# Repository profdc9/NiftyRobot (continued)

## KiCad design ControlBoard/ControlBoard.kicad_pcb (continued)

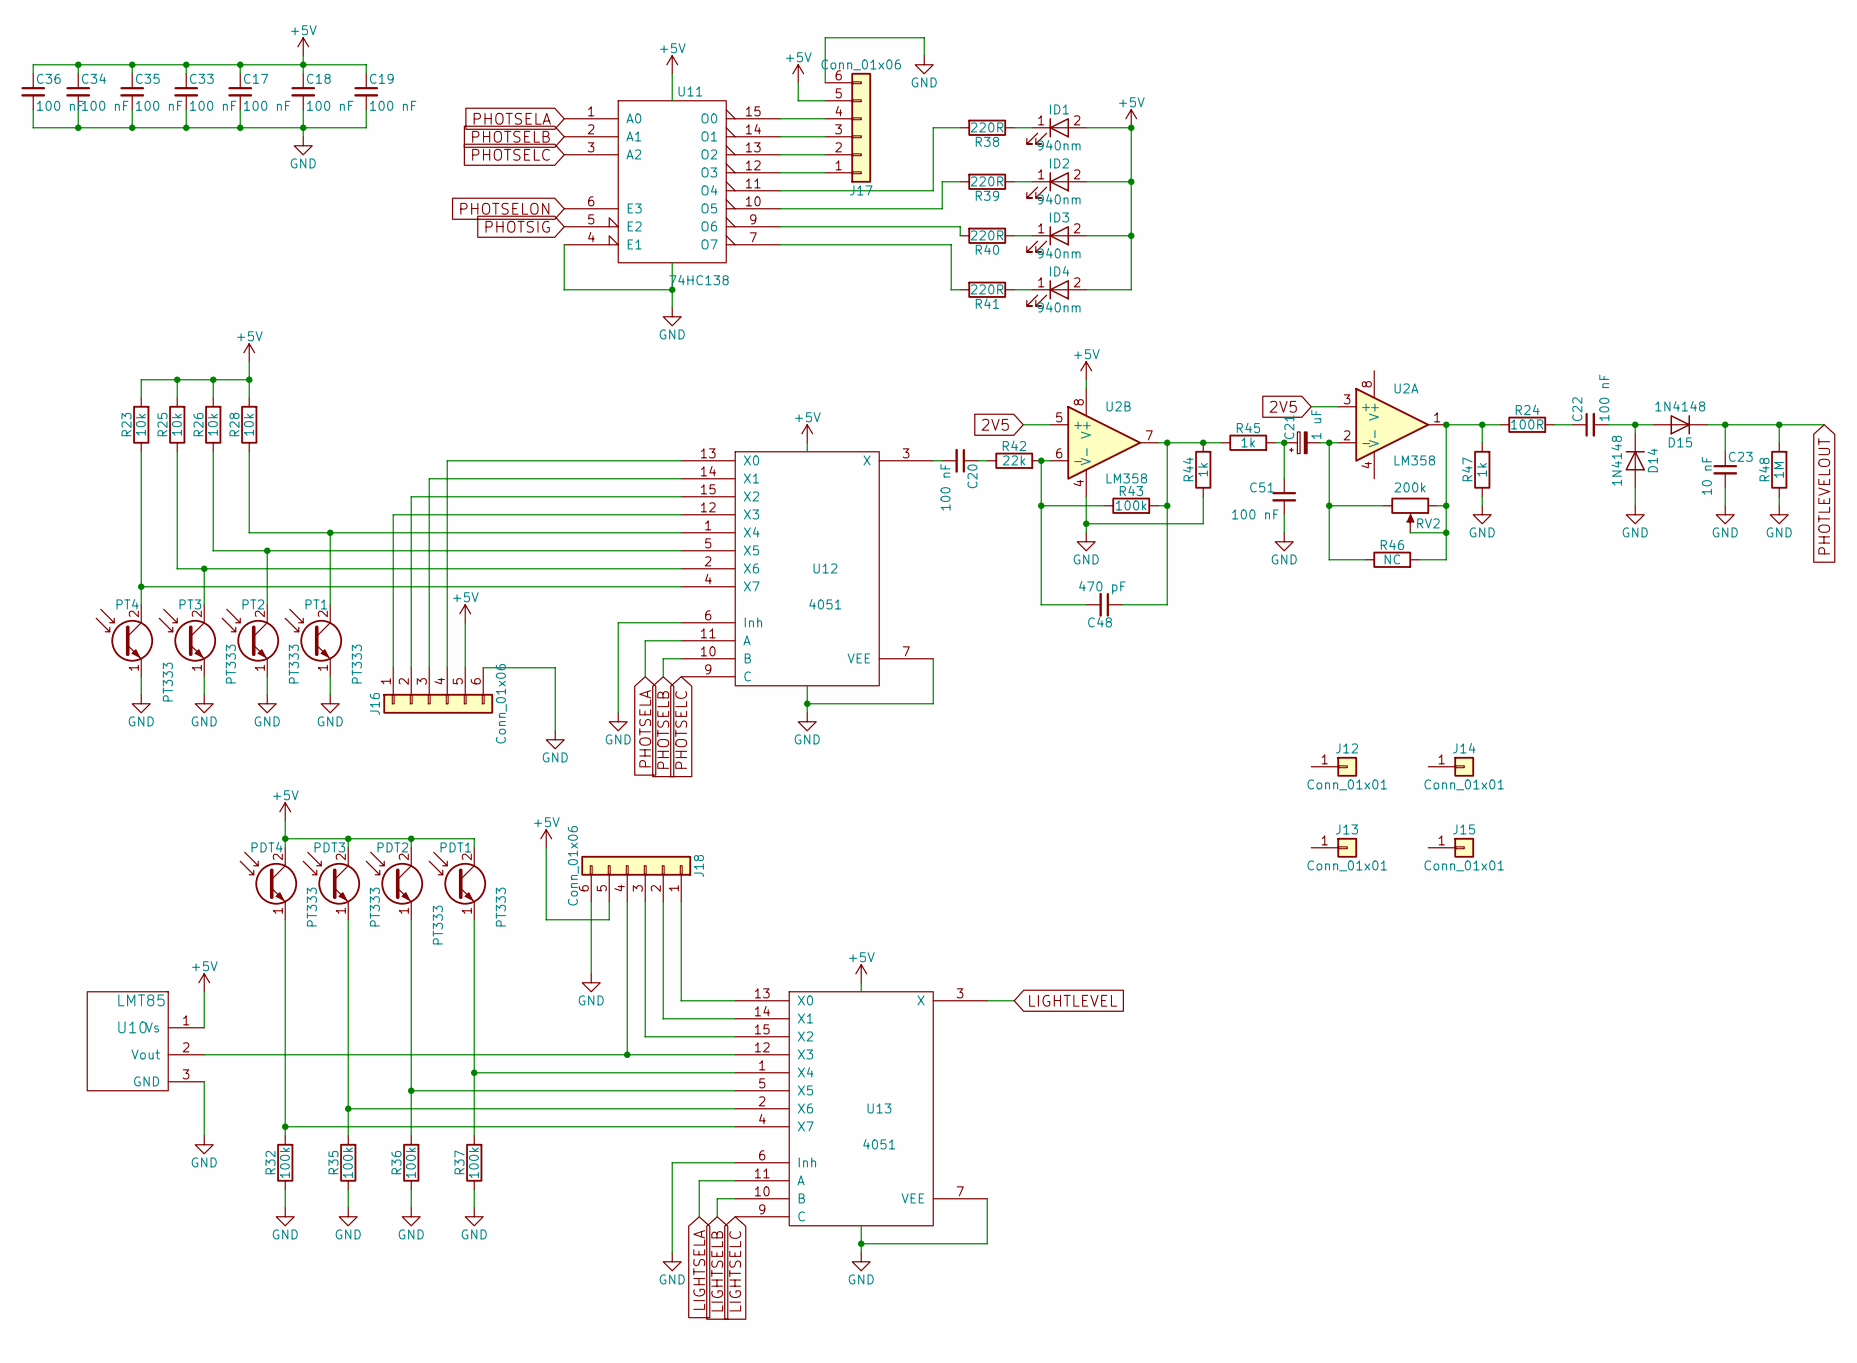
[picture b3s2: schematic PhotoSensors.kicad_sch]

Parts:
C17, C18, C19, C33, C34, C35, C36: 100 nF; C_Disc_D5.0mm_W2.5mm_P2.50mm
C20, C22, C51: 100 nF; C_Disc_D5.0mm_W2.5mm_P5.00mm
C21: 1 uF; CP_Radial_D5.0mm_P2.50mm
C23: 10 nF; C_Disc_D5.0mm_W2.5mm_P5.00mm
C48: 470 pF; C_Disc_D5.0mm_W2.5mm_P5.00mm
D14, D15: 1N4148; D_DO-41_SOD81_P7.62mm_Horizontal
ID1, ID2, ID3, ID4: 940nm; LED_D5.0mm
J12, J13, J14, J15: Conn_01x01; IRPair
J16, J17, J18: Conn_01x06; Pin_Header_Straight_1x06_Pitch2.54mm
PDT1, PDT2, PDT3, PDT4: PT333; LED_D5.0mm
PT1, PT2, PT3, PT4: PT333; LED_D5.0mm
R23, R25, R26, R28: 10k; R_Axial_DIN0207_L6.3mm_D2.5mm_P7.62mm_Horizontal
R24: 100R; R_Axial_DIN0207_L6.3mm_D2.5mm_P7.62mm_Horizontal
R32, R35, R36, R37, R43: 100k; R_Axial_DIN0207_L6.3mm_D2.5mm_P7.62mm_Horizontal
R38, R39, R40, R41: 220R; R_Axial_DIN0207_L6.3mm_D2.5mm_P7.62mm_Horizontal
R42: 22k; R_Axial_DIN0207_L6.3mm_D2.5mm_P7.62mm_Horizontal
R44, R45, R47: 1k; R_Axial_DIN0207_L6.3mm_D2.5mm_P7.62mm_Horizontal
R46: NC; R_Axial_DIN0207_L6.3mm_D2.5mm_P7.62mm_Horizontal
R48: 1M; R_Axial_DIN0207_L6.3mm_D2.5mm_P7.62mm_Horizontal
RV2: 200k; Potentiometer_Trimmer_Bourns_3296W
U2: LM358; DIP-8_W7.62mm_Socket
U10: LMT85; TO-92_Inline_Wide
U11: 74HC138; DIP-16_W7.62mm_Socket
U12, U13: 4051; DIP-16_W7.62mm_Socket

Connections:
2V5: U2.3 (+), U2.5 (+); also elsewhere on the board
+5V: C17.1, C18.1, C19.1, C33.1, C34.1, C35.1, C36.1, ID1.2 (A), ID2.2 (A), ID3.2 (A), ID4.2 (A), J16.5, J17.5, J18.5, PDT1.2 (C), PDT2.2 (C), PDT3.2 (C), PDT4.2 (C), R23.2, R25.2, R26.2, R28.2, U2.8 (V+), U10.1 (Vs), U11.16 (VCC), U12.16 (VDD), U13.16 (VDD); also elsewhere on the board
GND: C17.2, C18.2, C19.2, C23.2, C33.2, C34.2, C35.2, C36.2, C51.2, D14.2 (A), J16.6, J17.6, J18.6, PT1.1 (E), PT2.1 (E), PT3.1 (E), PT4.1 (E), R32.1, R35.1, R36.1, R37.1, R44.1, R47.1, R48.1, U2.4 (V-), U10.3 (GND), U11.4 (E1), U11.8 (GND), U12.6 (Inh), U12.7 (VEE), U12.8 (VSS), U13.6 (Inh), U13.7 (VEE), U13.8 (VSS); also elsewhere on the board
LIGHTLEVEL: U13.3 (X); also elsewhere on the board
LIGHTSELA: U13.11 (A); also elsewhere on the board
LIGHTSELB: U13.10 (B); also elsewhere on the board
LIGHTSELC: U13.9 (C); also elsewhere on the board
unnamed: C20.1, R42.1
unnamed: C21.1, C51.1, R45.2
unnamed: C22.1, R24.2
unnamed: C48.1, R43.2, R44.2, R45.1, U2.7
unnamed: C22.2, D14.1 (K), D15.2 (A)
unnamed: ID1.1 (K), R38.1
unnamed: ID2.1 (K), R39.1
unnamed: ID3.1 (K), R40.1
unnamed: ID4.1 (K), R41.1
unnamed: J16.1, U12.12 (X3)
unnamed: J16.2, U12.15 (X2)
unnamed: J16.3, U12.14 (X1)
unnamed: J16.4, U12.13 (X0)
unnamed: J17.1, U11.12 (O3)
unnamed: J17.2, U11.13 (O2)
unnamed: J17.3, U11.14 (O1)
unnamed: J17.4, U11.15 (O0)
unnamed: J18.1, U13.13 (X0)
unnamed: J18.2, U13.14 (X1)
unnamed: J18.3, U13.15 (X2)
unnamed: J18.4, U10.2 (Vout), U13.12 (X3)
unnamed: PDT1.1 (E), R37.2, U13.1 (X4)
unnamed: PDT2.1 (E), R36.2, U13.5 (X5)
unnamed: PDT3.1 (E), R35.2, U13.2 (X6)
unnamed: PDT4.1 (E), R32.2, U13.4 (X7)
unnamed: PT1.2 (C), R28.1, U12.1 (X4)
unnamed: PT2.2 (C), R26.1, U12.5 (X5)
unnamed: PT3.2 (C), R25.1, U12.2 (X6)
unnamed: PT4.2 (C), R23.1, U12.4 (X7)
unnamed: R24.1, R46.2, R47.2, RV2.1, RV2.2, U2.1
unnamed: C21.2, R46.1, RV2.3, U2.2 (-)
unnamed: C48.2, R42.2, R43.1, U2.6 (-)
unnamed: R38.2, U11.11 (O4)
unnamed: R39.2, U11.10 (O5)
unnamed: R40.2, U11.9 (O6)
unnamed: R41.2, U11.7 (O7)
unnamed: C20.2, U12.3 (X)
PHOTLEVELOUT: C23.1, D15.1 (K), R48.2; also elsewhere on the board
PHOTSELA: U11.1 (A0), U12.11 (A); also elsewhere on the board
PHOTSELB: U11.2 (A1), U12.10 (B); also elsewhere on the board
PHOTSELC: U11.3 (A2), U12.9 (C); also elsewhere on the board
PHOTSELON: U11.6 (E3); also elsewhere on the board
PHOTSIG: U11.5 (E2); also elsewhere on the board

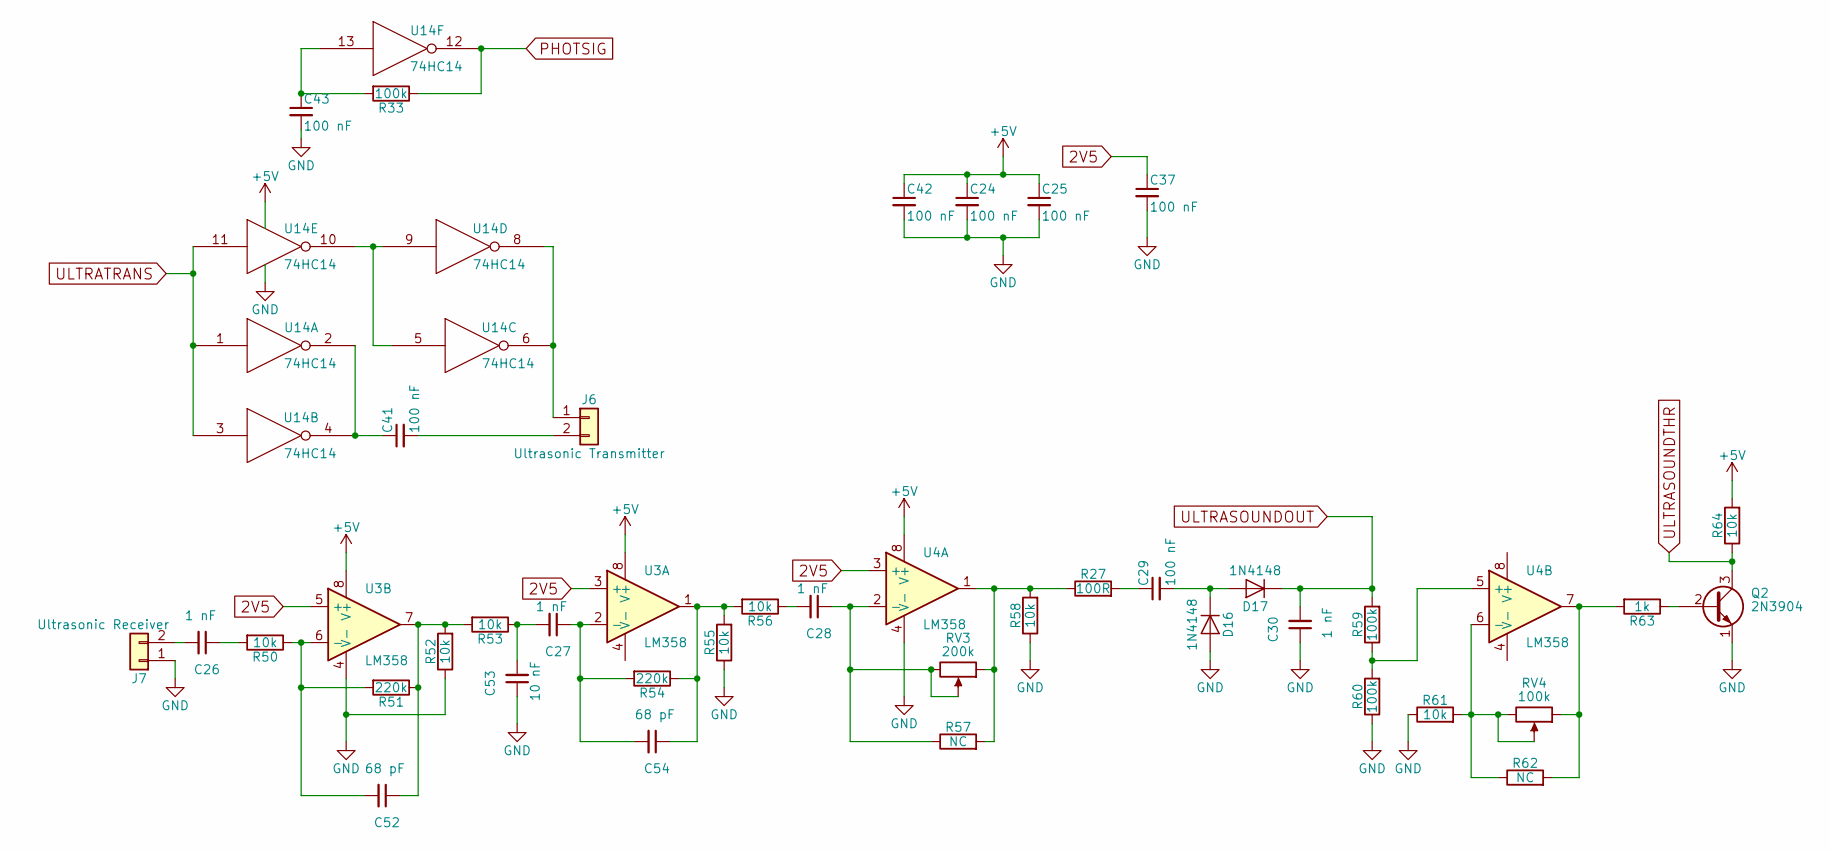
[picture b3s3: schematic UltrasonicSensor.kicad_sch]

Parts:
C24, C25, C29, C37, C41, C42, C43: 100 nF; C_Disc_D5.0mm_W2.5mm_P2.50mm
C26, C27, C28, C30: 1 nF; C_Disc_D5.0mm_W2.5mm_P5.00mm
C52, C54: 68 pF; C_Disc_D5.0mm_W2.5mm_P5.00mm
C53: 10 nF; C_Disc_D5.0mm_W2.5mm_P5.00mm
D16, D17: 1N4148; D_DO-41_SOD81_P7.62mm_Horizontal
J6: Ultrasonic Transmitter; TerminalBlock_bornier-2_P5.08mm
J7: Ultrasonic Receiver; TerminalBlock_bornier-2_P5.08mm
Q2: 2N3904; TO-92_Inline_Wide
R27: 100R; R_Axial_DIN0207_L6.3mm_D2.5mm_P7.62mm_Horizontal
R33, R59, R60: 100k; R_Axial_DIN0207_L6.3mm_D2.5mm_P7.62mm_Horizontal
R50, R52, R53, R55, R56, R58, R61, R64: 10k; R_Axial_DIN0207_L6.3mm_D2.5mm_P7.62mm_Horizontal
R51, R54: 220k; R_Axial_DIN0207_L6.3mm_D2.5mm_P7.62mm_Horizontal
R57, R62: NC; R_Axial_DIN0207_L6.3mm_D2.5mm_P7.62mm_Horizontal
R63: 1k; R_Axial_DIN0207_L6.3mm_D2.5mm_P7.62mm_Horizontal
RV3: 200k; Potentiometer_Trimmer_Bourns_3296W
RV4: 100k; Potentiometer_Trimmer_Bourns_3296W
U3, U4: LM358; DIP-8_W7.62mm_Socket
U14: 74HC14; DIP-14_W7.62mm_Socket

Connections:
2V5: C37.1, U3.3 (+), U3.5 (+), U4.3 (+); also elsewhere on the board
+5V: C24.1, C25.1, C42.1, R64.2, U3.8 (V+), U4.8 (V+), U14.14 (VCC); also elsewhere on the board
GND: C24.2, C25.2, C30.1, C37.2, C42.2, C43.2, C53.1, D16.2 (A), J7.1, Q2.1 (E), R52.1, R55.1, R58.1, R60.1, R61.1, U3.4 (V-), U4.4 (V-), U14.7 (GND); also elsewhere on the board
unnamed: C26.1, R50.2
unnamed: C27.2, C53.2, R53.1
unnamed: C28.2, R56.1
unnamed: C29.1, R27.2
unnamed: C41.1, U14.2, U14.4
unnamed: C43.1, R33.2, U14.13
unnamed: C52.1, R51.1, R52.2, R53.2, U3.7
unnamed: C54.1, R54.1, R55.2, R56.2, U3.1
unnamed: C29.2, D16.1 (K), D17.2 (A)
unnamed: J6.1, U14.6, U14.8
unnamed: C41.2, J6.2
unnamed: C26.2, J7.2
unnamed: Q2.2 (B), R63.1
unnamed: R27.1, R57.2, R58.2, RV3.1, U4.1
unnamed: R62.2, R63.2, RV4.1, U4.7
unnamed: C27.1, C54.2, R54.2, U3.2 (-)
unnamed: C52.2, R50.1, R51.2, U3.6 (-)
unnamed: C28.1, R57.1, RV3.2, RV3.3, U4.2 (-)
unnamed: R59.1, R60.2, U4.5 (+)
unnamed: R61.2, R62.1, RV4.2, RV4.3, U4.6 (-)
unnamed: U14.5, U14.9, U14.10
PHOTSIG: R33.1, U14.12; also elsewhere on the board
ULTRASOUNDOUT: C30.2, D17.1 (K), R59.2; also elsewhere on the board
ULTRASOUNDTHR: Q2.3 (C), R64.1; also elsewhere on the board
ULTRATRANS: U14.1, U14.3, U14.11; also elsewhere on the board

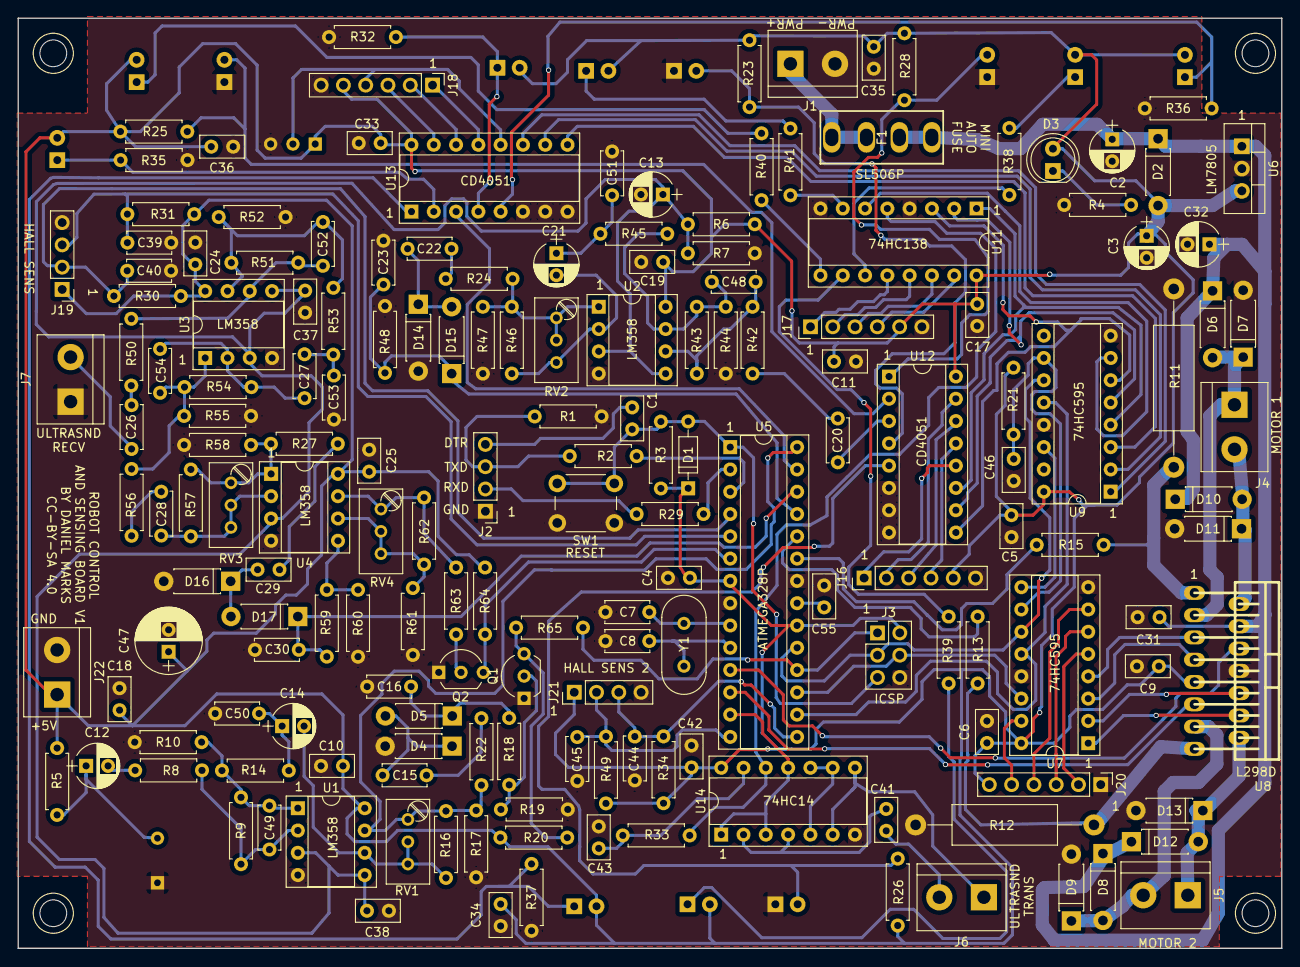
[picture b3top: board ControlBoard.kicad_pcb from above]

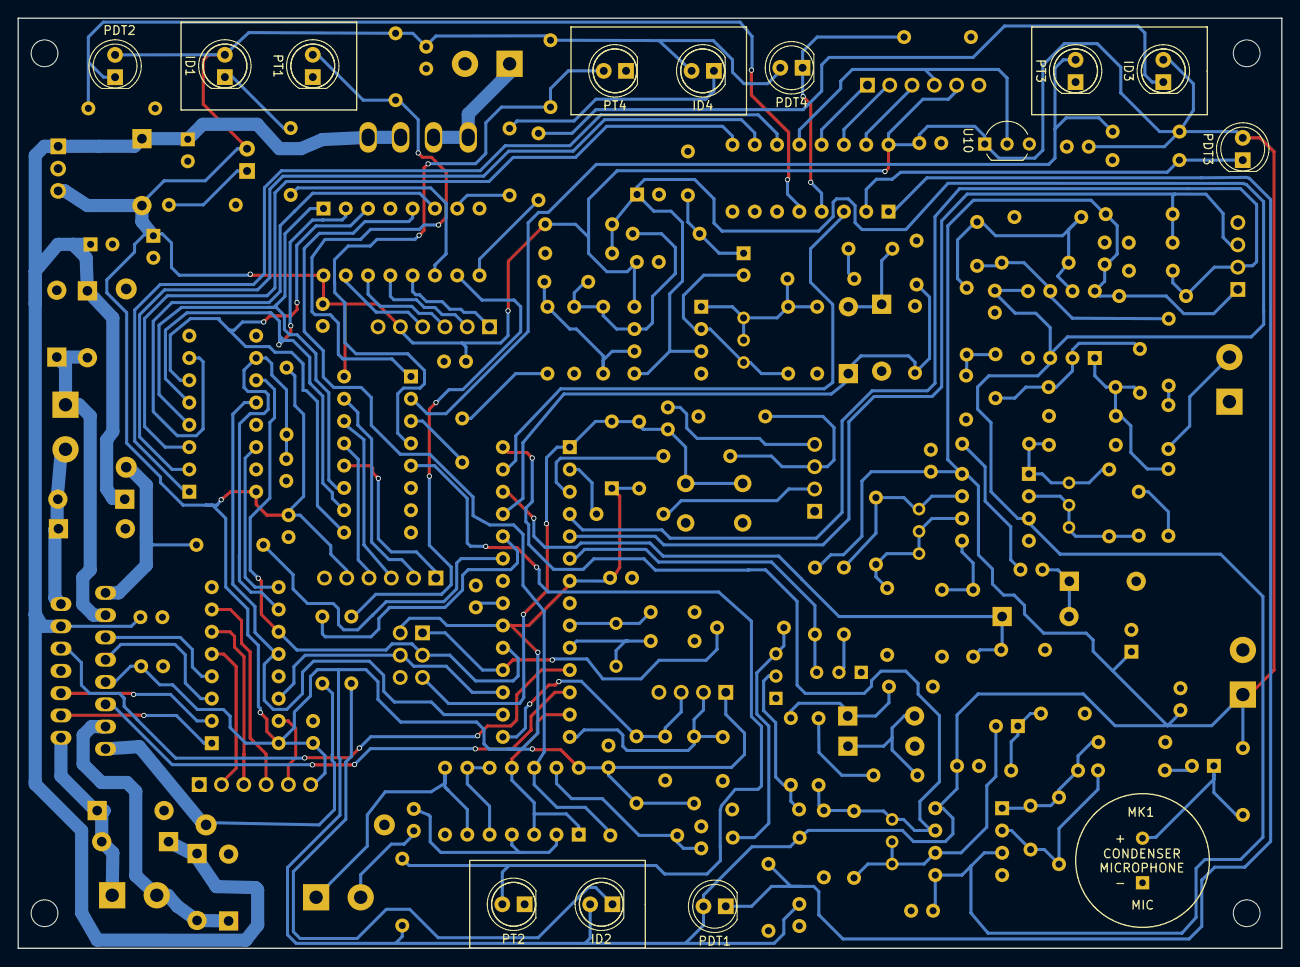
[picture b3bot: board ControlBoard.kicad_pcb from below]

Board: 2 copper layers, 144.0 x 106.0 mm, 195 parts (18 on the bottom side), 126 nets.

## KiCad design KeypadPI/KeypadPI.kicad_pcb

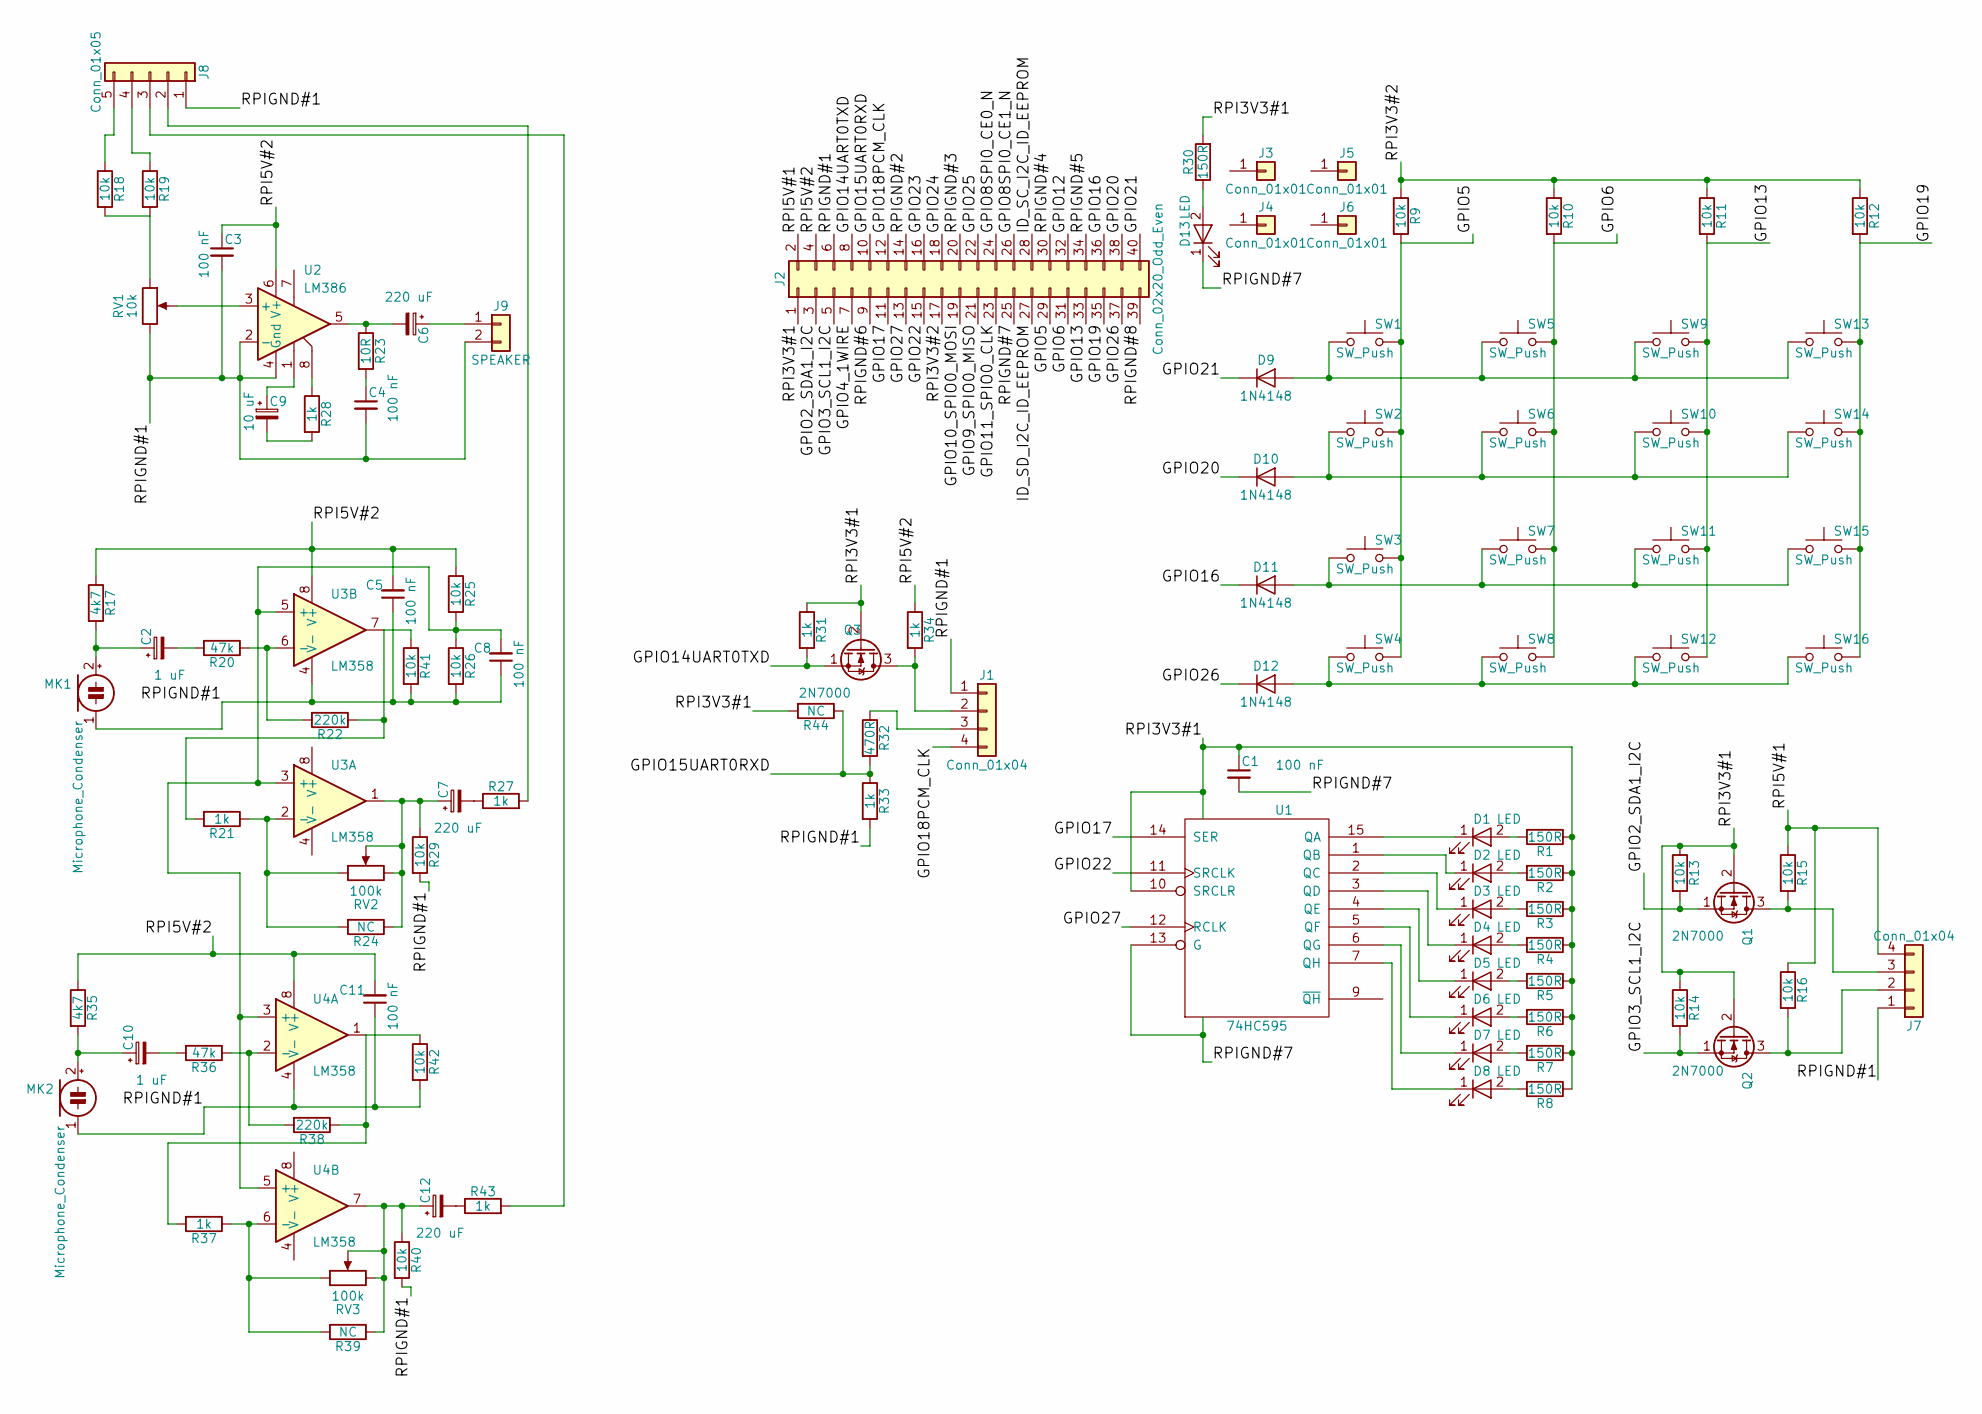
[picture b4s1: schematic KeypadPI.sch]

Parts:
C1, C3, C4, C5, C8, C11: 100 nF; C_Disc_D5.0mm_W2.5mm_P2.50mm
C2, C10: 1 uF; CP_Radial_D5.0mm_P2.50mm
C6, C7, C12: 220 uF; CP_Radial_D5.0mm_P2.50mm
C9: 10 uF; CP_Radial_D5.0mm_P2.50mm
D1, D2, D3, D4, D5, D6, D7, D8, D13: LED; LED_D5.0mm
D9, D10, D11, D12: 1N4148; D_DO-35_SOD27_P7.62mm_Horizontal
J1, J7: Conn_01x04; Pin_Header_Straight_1x04_Pitch2.54mm
J2: Conn_02x20_Odd_Even; Pin_Header_Straight_2x20_Pitch2.54mm
J3, J4, J5, J6: Conn_01x01; 1pin
J8: Conn_01x05; Pin_Header_Straight_1x05_Pitch2.54mm
J9: SPEAKER; TerminalBlock_bornier-2_P5.08mm
MK1, MK2: Microphone_Condenser; CondenserMic
Q1, Q2, Q3: 2N7000; TO-92_Inline_Wide
R1, R2, R3, R4, R5, R6, R7, R8, R30: 150R; R_Axial_DIN0207_L6.3mm_D2.5mm_P7.62mm_Horizontal
R9, R10, R11, R12, R13, R14, R15, R16, R18, R19, R25, R26, R29, R40, R41, R42: 10k; R_Axial_DIN0207_L6.3mm_D2.5mm_P7.62mm_Horizontal
R17, R35: 4k7; R_Axial_DIN0207_L6.3mm_D2.5mm_P7.62mm_Horizontal
R20, R36: 47k; R_Axial_DIN0207_L6.3mm_D2.5mm_P7.62mm_Horizontal
R21, R27, R28, R31, R33, R34, R37, R43: 1k; R_Axial_DIN0207_L6.3mm_D2.5mm_P7.62mm_Horizontal
R22, R38: 220k; R_Axial_DIN0207_L6.3mm_D2.5mm_P7.62mm_Horizontal
R23: 10R; R_Axial_DIN0207_L6.3mm_D2.5mm_P7.62mm_Horizontal
R24, R39, R44: NC; R_Axial_DIN0207_L6.3mm_D2.5mm_P7.62mm_Horizontal
R32: 470R; R_Axial_DIN0207_L6.3mm_D2.5mm_P7.62mm_Horizontal
RV1: 10k; Potentiometer_Trimmer_Bourns_3296W
RV2, RV3: 100k; Potentiometer_Trimmer_Bourns_3296W
SW1, SW2, SW3, SW4, SW5, SW6, SW7, SW8, SW9, SW10, SW11, SW12, SW13, SW14, SW15, SW16: SW_Push; SW_PUSH_6mm
U1: 74HC595; DIP-16_W7.62mm_Socket
U2: LM386; DIP-8_W7.62mm_Socket
U3, U4: LM358; DIP-8_W7.62mm_Socket

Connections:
/GPIO2_SDA1_I2C: J2.3, Q1.1 (S), R13.2
/GPIO3_SCL1_I2C: J2.5, Q2.1 (S), R14.2
/GPIO4_1WIRE: J2.7
/GPIO5: J2.29, R9.2, SW1.2, SW2.2, SW3.2, SW4.2
/GPIO6: J2.31, R10.2, SW5.2, SW6.2, SW7.2, SW8.2
/GPIO8SPI0_CE0_N: J2.24
/GPIO8SPI0_CE1_N: J2.26
/GPIO9_SPIO0_MISO: J2.21
/GPIO10_SPIO0_MOSI: J2.19
/GPIO11_SPIO0_CLK: J2.23
/GPIO12: J2.32
/GPIO13: J2.33, R11.2, SW9.2, SW10.2, SW11.2, SW12.2
/GPIO14UART0TXD: J2.8, Q3.1 (S), R31.2
/GPIO15UART0RXD: J2.10, R32.2, R33.1, R44.1
/GPIO16: D11.1 (K), J2.36
/GPIO17: J2.11, U1.14 (SER)
/GPIO18PCM_CLK: J1.4, J2.12
/GPIO19: J2.35, R12.2, SW13.2, SW14.2, SW15.2, SW16.2
/GPIO20: D10.1 (K), J2.38
/GPIO21: D9.1 (K), J2.40
/GPIO22: J2.15, U1.11 (SRCLK)
/GPIO23: J2.16
/GPIO24: J2.18
/GPIO25: J2.22
/GPIO26: D12.1 (K), J2.37
/GPIO27: J2.13, U1.12 (RCLK)
/ID_SC_I2C_ID_EEPROM: J2.28
/ID_SD_I2C_ID_EEPROM: J2.27
/RPI3V3#2: J2.17, R9.1, R10.1, R11.1, R12.1
/RPI5V#1: J2.2, J7.4, R15.1, R16.1
/RPI5V#2: C3.1, C5.2, C11.2, J2.4, R17.1, R25.1, R34.1, R35.1, U2.6 (V+), U3.8 (V+), U4.8 (V+)
/RPIGND#1: C3.2, C4.2, C5.1, C8.1, C11.1, J1.1, J2.6, J7.1, J8.1, J9.2, MK1.1 (-), MK2.1 (-), R26.2, R29.2, R33.2, R40.2, R41.2, R42.2, RV1.3, U2.2 (-), U2.4 (Gnd), U3.4 (V-), U4.4 (V-)
/RPIGND#2: J2.14
/RPIGND#3: J2.20
/RPIGND#4: J2.30
/RPIGND#5: J2.34
/RPIGND#6: J2.9
/RPIGND#8: J2.39
GND: C1.2, D13.1 (K), J2.25, U1.8 (GND), U1.13 (G)
unnamed: C2.1, MK1.2 (+), R17.2
unnamed: C2.2, R20.2
unnamed: C4.1, R23.2
unnamed: C6.1, J9.1
unnamed: C6.2, R23.1, U2.5
unnamed: C7.1, R24.1, R29.1, RV2.2, RV2.3, U3.1
unnamed: C7.2, R27.1
unnamed: C8.2, R25.2, R26.1, U3.3 (+), U3.5 (+), U4.3 (+), U4.5 (+)
unnamed: C9.1, U2.1
unnamed: C9.2, R28.2
unnamed: C10.1, MK2.2 (+), R35.2
unnamed: C10.2, R36.2
unnamed: C12.1, R39.1, R40.1, RV3.2, RV3.3, U4.7
unnamed: C12.2, R43.1
unnamed: D1.1 (K), U1.15 (QA)
unnamed: D1.2 (A), R1.2
unnamed: D2.1 (K), U1.1 (QB)
unnamed: D2.2 (A), R2.2
unnamed: D3.1 (K), U1.2 (QC)
unnamed: D3.2 (A), R3.2
unnamed: D4.1 (K), U1.3 (QD)
unnamed: D4.2 (A), R4.2
unnamed: D5.1 (K), U1.4 (QE)
unnamed: D5.2 (A), R5.2
unnamed: D6.1 (K), U1.5 (QF)
unnamed: D6.2 (A), R6.2
unnamed: D7.1 (K), U1.6 (QG)
unnamed: D7.2 (A), R7.2
unnamed: D8.1 (K), U1.7 (QH)
unnamed: D8.2 (A), R8.2
unnamed: D9.2 (A), SW1.1, SW5.1, SW9.1, SW13.1
unnamed: D10.2 (A), SW2.1, SW6.1, SW10.1, SW14.1
unnamed: D11.2 (A), SW3.1, SW7.1, SW11.1, SW15.1
unnamed: D12.2 (A), SW4.1, SW8.1, SW12.1, SW16.1
unnamed: D13.2 (A), R30.1
unnamed: J1.2, Q3.3 (D), R34.2
unnamed: J1.3, R32.1
unnamed: J7.2, Q2.3 (D), R16.2
unnamed: J7.3, Q1.3 (D), R15.2
unnamed: J8.2, R27.2
unnamed: J8.3, R43.2
unnamed: J8.4, R19.1
unnamed: J8.5, R18.1
unnamed: R18.2, R19.2, RV1.1
unnamed: R20.1, R22.2, U3.6 (-)
unnamed: R21.1, R24.2, RV2.1, U3.2 (-)
unnamed: R21.2, R22.1, R41.1, U3.7
unnamed: R28.1, U2.8
unnamed: R36.1, R38.2, U4.2 (-)
unnamed: R37.1, R39.2, RV3.1, U4.6 (-)
unnamed: R37.2, R38.1, R42.1, U4.1
unnamed: RV1.2, U2.3 (+)
VCC: C1.1, J2.1, Q1.2 (G), Q2.2 (G), Q3.2 (G), R1.1, R2.1, R3.1, R4.1, R5.1, R6.1, R7.1, R8.1, R13.1, R14.1, R30.2, R31.1, R44.2, U1.10 (SRCLR), U1.16 (VCC)

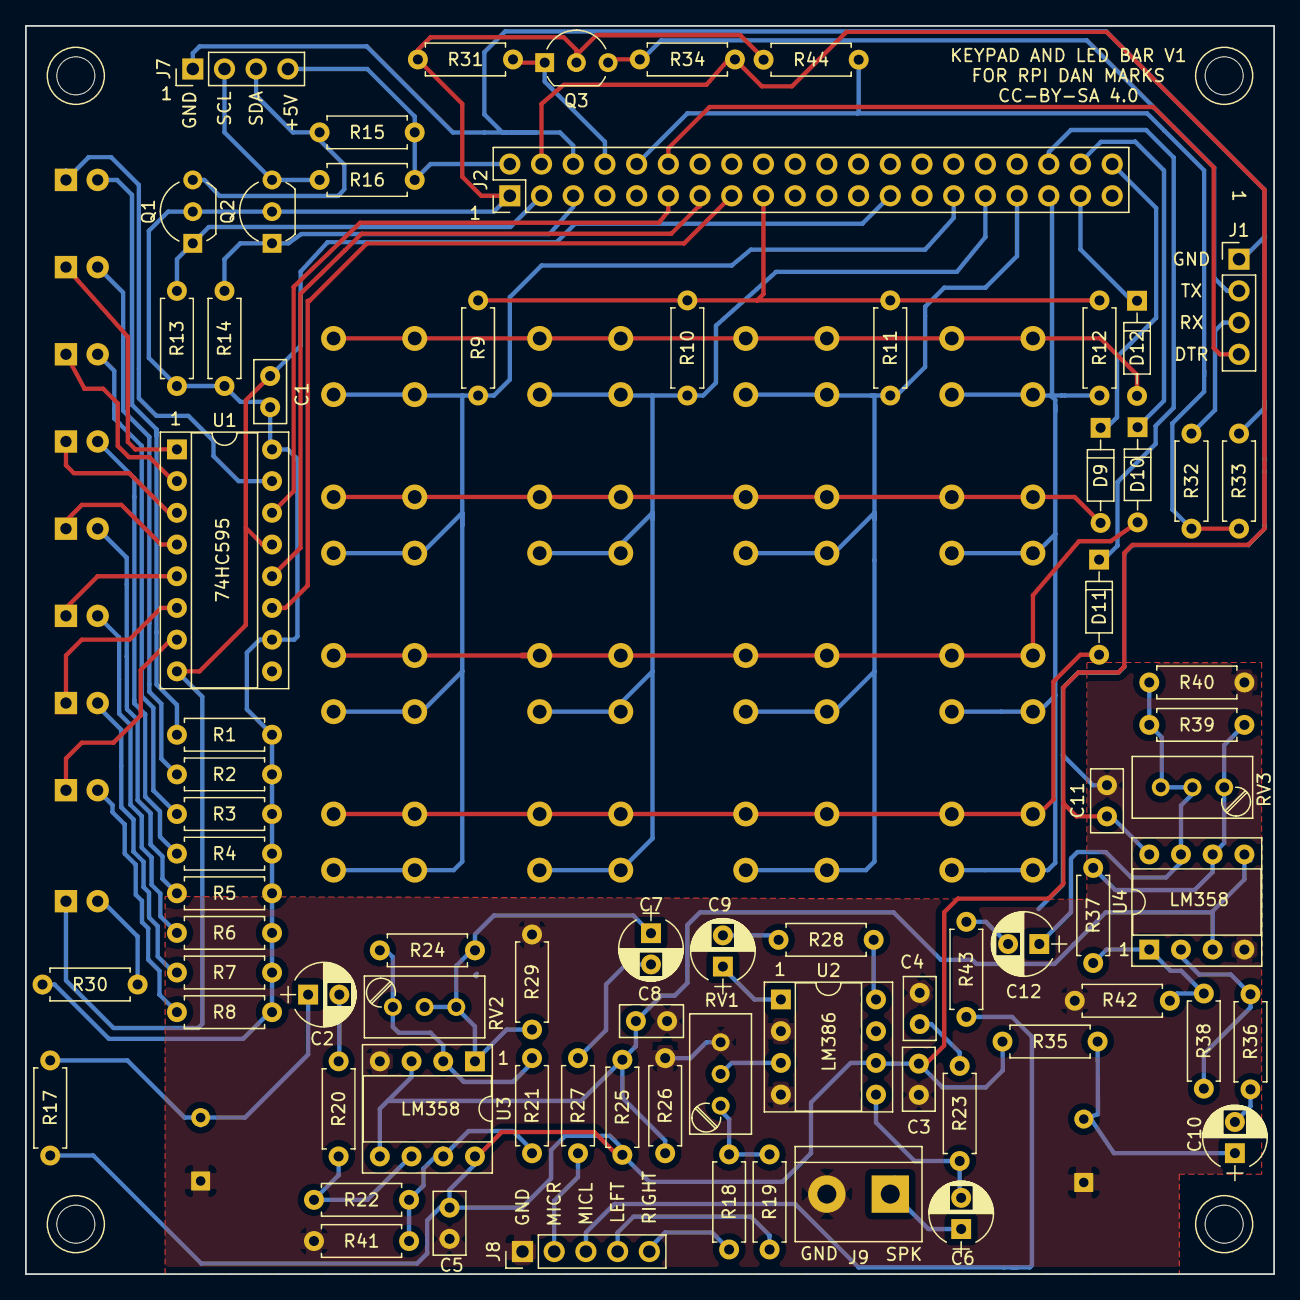
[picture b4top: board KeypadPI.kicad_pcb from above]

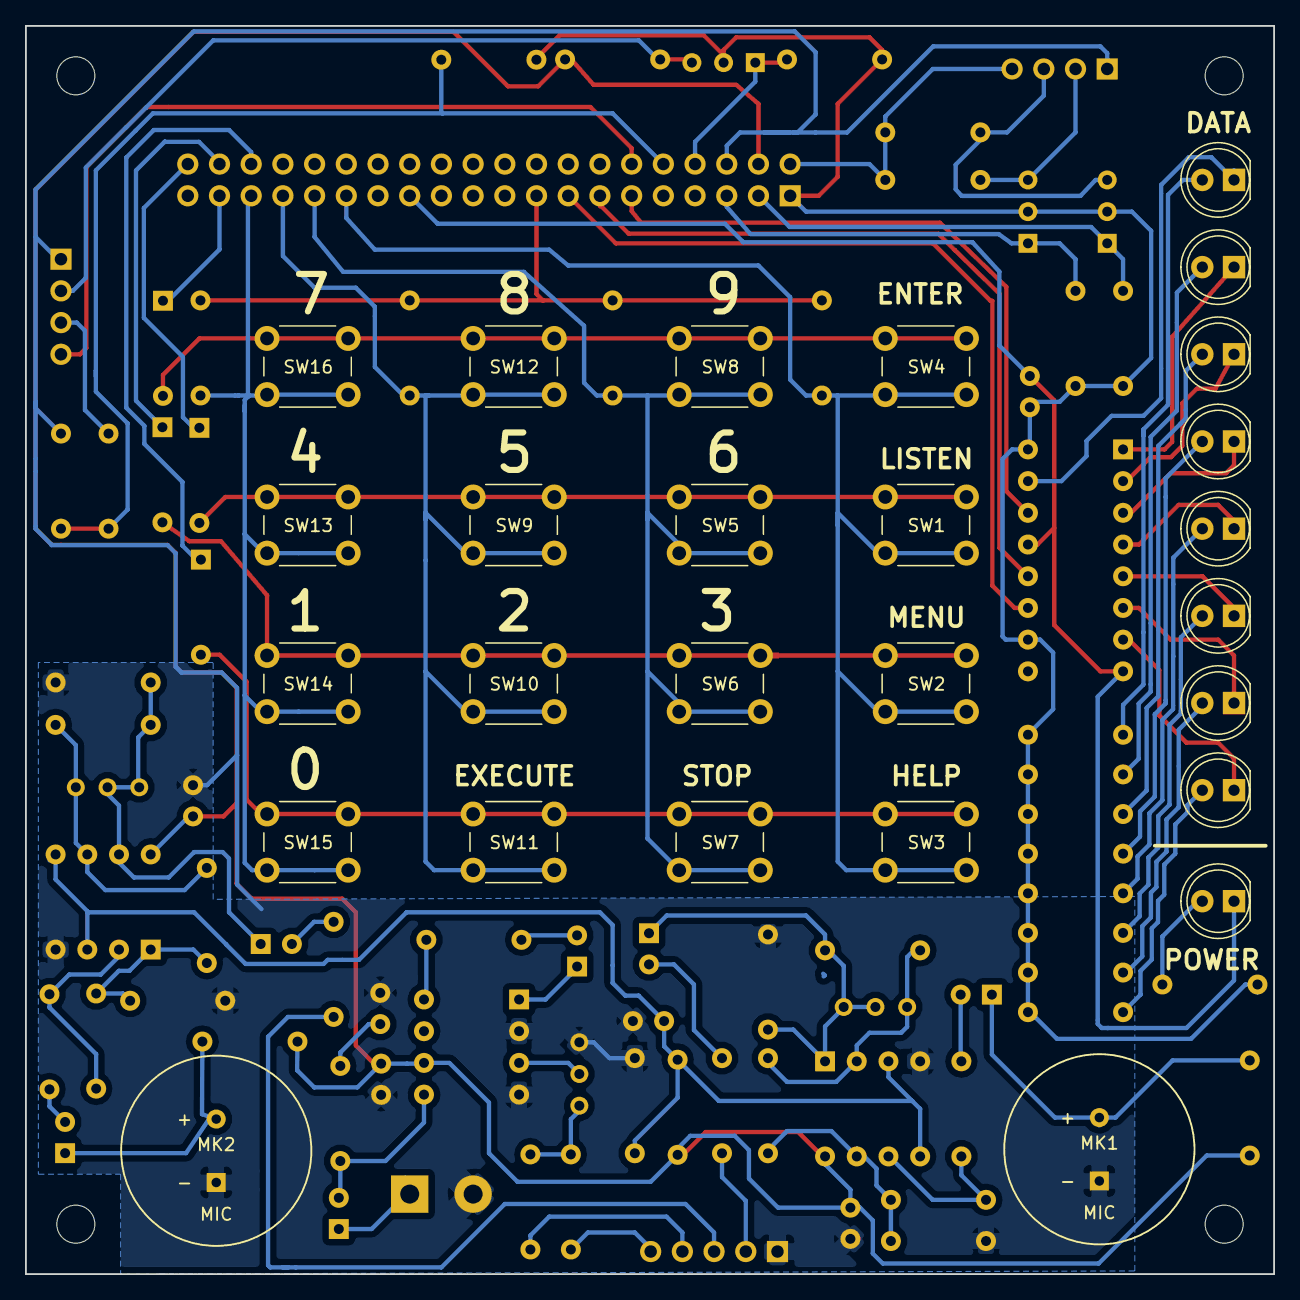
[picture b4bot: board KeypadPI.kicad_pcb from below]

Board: 2 copper layers, 100.0 x 100.0 mm, 106 parts (27 on the bottom side), 74 nets.

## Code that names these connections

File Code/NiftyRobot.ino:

#include <Arduino.h>
#include <wiring_private.h>
#include <SPI.h>

#include "consoleio.h"
#include "tinycl.h"

#define CURSEN1 A0
#define CURSEN2 A1
#define PHOTLEVELOUT A2
#define ULTRASOUNDOUT A3
#define LIGHTLEVEL A4
#define MICOUT A5

#define ADCCURSEN1 0
#define ADCCURSEN2 1
#define ADCPHOTLEVELOUT 2
#define ADCULTRASOUNDOUT 3
#define ADCLIGHTLEVEL 4
#define ADCMICOUT 5

#define HALLSENS1_1 2
#define HALLSENS1_2 3
#define ULTRASOUNDTHR 4
#define MOTORPWM1 5
#define MOTORPWM2 6
#define ULTRATRANS 7
#define HALLSENS2_1 8
#define HALLSENS2_2 9
#define LATCH 10
#define MOSI 11
#define MICTHR 12
#define SCK 13

uint16_t quickADC(uint8_t ch)
{
  uint8_t low, high;
  ADMUX = (1 << REFS0) | ch;
  sbi(ADCSRA, ADSC);
  while (bit_is_set(ADCSRA, ADSC));
  low = ADCL;
  high = ADCH;
  return (((uint16_t)high) << 8) | low;
}

uint16_t quickADCmult(uint8_t ch, uint8_t rep)
{
  uint16_t ct = 0;
  while (rep > 0)
  {
    rep--;
    ct += quickADC(ch);
  }
  return ct;
}

void fastADC() {
  ADMUX = (1 << REFS0);
  ADCSRB = 0;
  ADCSRA = (1 << ADEN) | (1 << ADPS2) | (1 << ADPS0);
}


uint8_t spi_outputs[2];

void transfer_spi_outputs(void)
{
  SPI.transfer(spi_outputs[1]);
  SPI.transfer(spi_outputs[0]);
  digitalWrite(LATCH, HIGH);
  digitalWrite(LATCH, LOW);
}

void motor_1_dir(uint8_t dir)
{
  spi_outputs[0] = (spi_outputs[0] & 0xE7) | (dir << 3);
}

void motor_2_dir(uint8_t dir)
{
  spi_outputs[0] = (spi_outputs[0] & 0xF9) | (dir << 1);
}

void select_light_detector(uint8_t det)
{
  const uint8_t det_ary[8] = { 0x00, 0x08, 0x04, 0x0C, 0x02, 0x0A, 0x06, 0x0E };
  spi_outputs[1] = (spi_outputs[1] & 0xF1) | (det << 1);
}

void select_ambient_detector(uint8_t amb, uint8_t on)
{
  const uint8_t amb_ary[8] = { 0x00, 0x40, 0x20, 0x60, 0x10, 0x50, 0x30, 0x70 };
  spi_outputs[1] = (spi_outputs[1] & 0x0F) | (amb << 4) | (on ? 0x80 : 0x00);
}

uint16_t read_light_detector(uint8_t det)
{
  select_ambient_detector(det, 1);
  transfer_spi_outputs();
  delay(100);
  return quickADCmult(ADCPHOTLEVELOUT,50);
}

void ultrasonic_range(uint16_t *range, uint16_t *maxmag)
{
  uint8_t i;
  uint8_t j;
  uint8_t p0 = PORTD & 0x7F;
  uint8_t p1 = p0 | 0x80;
  noInterrupts();
  for (i=10;i>0;i--)
  {
    PORTD = p1;
    for (j=49;j>0;j--)
       __asm__ __volatile__ ("nop\n\t");
    PORTD = p0;
    for (j=49;j>0;j--)
       __asm__ __volatile__ ("nop\n\t");
  }
  interrupts();
  delayMicroseconds(2000);
  ADMUX = (1 << REFS0) | ADCULTRASOUNDOUT;
  
  uint16_t maxval = 0;
  uint32_t starttime = micros();
  uint32_t maxtime = starttime;
  for (uint16_t j=1000;j>0;j--)
  {  
    uint8_t low, high;
    uint16_t val;
    sbi(ADCSRA, ADSC);
    while (bit_is_set(ADCSRA, ADSC));
    low = ADCL;
    high = ADCH;
    val = (((uint16_t)high) << 8) | low;
    if (val > maxval)
    {
      maxval = val;
      maxtime = micros();
    }
  }
  *range = (maxtime - starttime) + 2000;
  *maxmag = maxval;
  return;
}

void setup() {
  Serial.begin(115200);
  console_setMainSerial(&Serial);
  SPI.begin();
  fastADC();
  pinMode(CURSEN1, INPUT);
  pinMode(CURSEN2, INPUT);
  pinMode(PHOTLEVELOUT, INPUT);
  pinMode(ULTRASOUNDOUT, INPUT);
  pinMode(LIGHTLEVEL, INPUT);
  pinMode(MICOUT, INPUT);
  pinMode(HALLSENS1_1, INPUT);
  pinMode(HALLSENS1_2, INPUT);
  pinMode(ULTRASOUNDTHR, INPUT);
  pinMode(MOTORPWM1, OUTPUT);
  pinMode(MOTORPWM2, OUTPUT);
  pinMode(ULTRATRANS, OUTPUT);
  pinMode(HALLSENS2_1, INPUT);
  pinMode(HALLSENS2_2, INPUT);
  pinMode(LATCH, OUTPUT);
  pinMode(MOSI, OUTPUT);
  pinMode(MICTHR, INPUT);
  pinMode(SCK, OUTPUT);
  digitalWrite(MOTORPWM1, LOW);
  digitalWrite(MOTORPWM2, LOW);
}

void print_vals(uint8_t c)
{
  uint16_t range,maxval;
  ultrasonic_range(&range, &maxval);
  Serial.print("range: ");
  Serial.print(range);
  Serial.print(" maxval: ");
  Serial.println(maxval);
  while (c > 0)
  {
    c--;
    delay(250);
    uint16_t d1 = read_light_detector(4);
    uint16_t d2 = read_light_detector(5);
    uint16_t d3 = read_light_detector(6);
    uint16_t d4 = read_light_detector(7);
    Serial.print("detectors: ");
    Serial.print(d1);
    Serial.print(" ");
    Serial.print(d2);
    Serial.print(" ");
    Serial.print(d3);
    Serial.print(" ");
    Serial.println(d4);
  }
}

int print_cmd(int args, tinycl_parameter* tp, void *v)
{
  int n = tp[0].ti.i;

  console_print("Number: ");
  console_println(n);
  return 1;
}

const tinycl_command tcmds[] =
{
  { "PRINT", "Print Number", print_cmd, TINYCL_PARM_INT, TINYCL_PARM_END },
  { "HELP", "Display This Help", help_cmd, {TINYCL_PARM_END } },
};

int help_cmd(int args, tinycl_parameter *tp, void *v)
{
  tinycl_print_commands(sizeof(tcmds) / sizeof(tinycl_command), tcmds);
  return 1;
}

void loop() {

  if (tinycl_task(sizeof(tcmds) / sizeof(tinycl_command), tcmds, NULL))
  {
    tinycl_do_echo = 1;
    console_print("> ");
  }

  print_vals(1);
  motor_1_dir(0);
  motor_2_dir(0);
  transfer_spi_outputs();
  Serial.print("dir1 ");
  Serial.println(spi_outputs[0], HEX);
  analogWrite(MOTORPWM1, 128);
  analogWrite(MOTORPWM2, 128);

  print_vals(1);
  motor_1_dir(0);
  motor_2_dir(0);
  transfer_spi_outputs();
  Serial.print("dir2 ");
  Serial.println(spi_outputs[0], HEX);
  analogWrite(MOTORPWM1, 128);
  analogWrite(MOTORPWM2, 128);
}

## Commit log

2021-09-24 Added CAD models
2021-09-25 Added KeypadPI
2021-09-26 Added audio input and output to keypad PCB
2021-09-26 Added second microphone to keypad
2021-09-27 A few fixes
2021-10-04 JLCPCB order 2021-10-03
2021-10-10 Added CAD files
2021-11-20 Begin code for controlling robot with command line
2022-01-11 Added some filter capacitors
2022-01-12 Added capacitor for AREF
2025-10-23 new commit
2026-02-07 Added experimental ultrasonic phased array
